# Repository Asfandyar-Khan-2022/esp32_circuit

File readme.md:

<video loop src="https://cdn.discordapp.com/attachments/1022999502975664129/1327480523676979220/esp32_front_pcb_360.mp4?ex=67833814&is=6781e694&hm=28d8638278647dbc779c7d77384b581d35094b70810547bf134dc499996c9c21&">  video </video>

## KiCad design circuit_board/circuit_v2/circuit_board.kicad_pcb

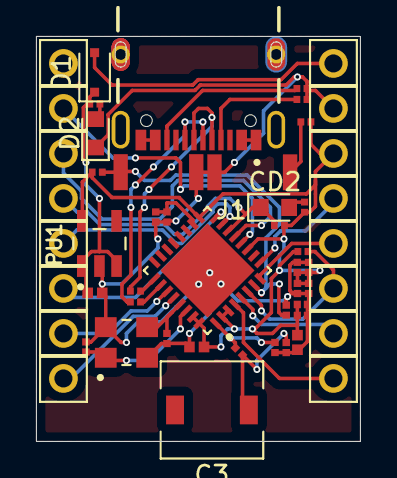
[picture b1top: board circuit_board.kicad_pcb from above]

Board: 2 copper layers, 18.0 x 22.5 mm, 53 parts (0 on the bottom side), 31 nets.

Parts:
C1, C2: C; CAPC0603X33N
C3: Antenna; L_Wuerth_HCI-5040
CD2: LED; LED_0603_1608Metric
D1: NRVA4004T3G; D_SOD-323F
D2: LED; LED_0603_1608Metric
H1, H16: 1; Pin_D1.1mm_L8.5mm_W2.5mm_FlatFork
H2, H12: 2; Pin_D1.1mm_L8.5mm_W2.5mm_FlatFork
H3, H15: 3; Pin_D1.1mm_L8.5mm_W2.5mm_FlatFork
H4, H11: 4; Pin_D1.1mm_L8.5mm_W2.5mm_FlatFork
H5, H14: 5; Pin_D1.1mm_L8.5mm_W2.5mm_FlatFork
H6, H10: 6; Pin_D1.1mm_L8.5mm_W2.5mm_FlatFork
H7, H13: 7; Pin_D1.1mm_L8.5mm_W2.5mm_FlatFork
H8, H9: 8; Pin_D1.1mm_L8.5mm_W2.5mm_FlatFork
J1: USB_C_Receptacle_USB2.0_16P; GCT_USB4105GFA
K1, K2: SW_Omron_B3FS; SKRK
PC1, PC2: C; CAPC1005X55N
PU1: ME6211C33M5; SOT95P280X145-5N
U1: ESP32-C3; QFN32_5X5MM
UC1, UC2, UC5, UC6, UC7, UC8, UC9, UC10, UC11, UC12, UC13: C; CAPC0603X33N
UC4: C; CAPC1005X55N
UR1, UR2, UR3, UR4, UR5, UR7, UR8, UR9, UR10, UR15: R; RESC0603X26N
UR6: 10; RESC0603X26N
Y1: NX3225SA-40M-EXS00A-CS03880; OSCCC320X250X60

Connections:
+3.3V: H6.1, PC2.1, PU1.5 (V_{OUT}), U1.2 (VDD3P3), U1.3 (VDD3P3), U1.11 (VDD3P3_RTC), U1.17 (VDD3P3_CPU), U1.31 (VDDA), U1.32 (VDDA), UC1.2, UC2.2, UC4.1, UC5.1, UC6.1, UC12.1, UC13.2, UR5.1, UR6.1, UR8.1, UR10.1, UR15.1
CC1: J1.A5 (CC1), UR1.1
CC2: J1.B5 (CC2), UR4.1
CHIP EN: K2.2, U1.7 (CHIP_EN), UC7.1, UR5.2
GND: C1.2, C2.2, D2.1 (K), H7.1, K1.1, K2.1, PC1.2, PC2.2, PU1.2 (V_{SS}), U1.33 (GND), UC1.1, UC2.1, UC4.2, UC5.2, UC6.2, UC7.2, UC8.2, UC9.2, UC10.2, UC11.2, UC12.2, UC13.1, UR1.2, UR4.2, Y1.2, Y1.4
GPIO0/U1TXD: H1.1, U1.4 (XTAL_32K_P)
GPIO1/U1RXD: H2.1, U1.5 (XTAL_32K_N)
GPIO2: H3.1, U1.6 (GPIO2), UR15.2
GPIO3: H4.1, U1.8 (GPIO3)
GPIO4/ADC1/SDA: H5.1, U1.9 (MTMS)
GPIO6: H12.1, U1.12 (MTCK)
GPIO7: H15.1, U1.13 (MTDO)
GPIO8/PWM: CD2.1 (K), H11.1, U1.14 (GPIO8), UR10.2
GPIO9: K1.2, UR6.2
GPIO9/BOOT: H14.1, U1.15 (GPIO9)
GPIO10: H10.1, U1.16 (GPIO10)
GPIO20: H13.1, U1.27 (U0RXD)
GPIO21: H9.1, U1.28 (U0TXD)
unnamed: C3.1 (A), UC8.1, UR9.2
unnamed: CD2.2 (A), UR8.2
unnamed: D2.2 (A), UR7.2
unnamed: J1.A6 (D+), J1.B6 (D+), UR3.1
unnamed: J1.A7 (D-), J1.B7 (D-), UR2.1
unnamed: U1.1 (LNA_IN), UC9.1, UR9.1
USBD_N: U1.25 (GPIO18), UR2.2
USBD_P: U1.26 (GPIO19), UR3.2
VBUS: D1.2 (A), H8.1
VDD SPI/GPIO11: U1.18 (VDD_SPI), UC10.1, UC11.1
VSYS: D1.1 (K), PC1.1, PU1.1 (V_{IN}), PU1.3 (CE), UR7.1
XTAL_N: C2.1, U1.29 (XTAL_N), Y1.3
XTAL_P: C1.1, U1.30 (XTAL_P), Y1.1

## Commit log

2025-01-08 adding all files
2025-01-09 backups save lives
2025-01-10 made a lot of changes
2025-01-11 made changes
2025-01-11 video
2025-01-11 added video link
